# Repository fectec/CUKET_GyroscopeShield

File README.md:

# MO-2 Gyroscope Verification Shield

<p align="justify">
The PCB is designed as a shield for the NUCLEO-F446RET6, mechanically capable of stacking directly on top of the development board. This configuration routes all power and communication signals from the microcontroller to the peripheral components without the need for external jumper wires.
</p>

<p align="center">

  <br>

  <br>
  <em>Figure 1: PCB manufacturing and integration stages.</em>
</p>

<p align="center">

  <br>

  <br>
  <em>Figure 2: Lateral profiles of the soldered system.</em>
</p>

<p align="justify">
The communication architecture relies on two distinct protocols: I<sup>2</sup>C for the Pmod gyroscope interface and SPI for the flash memory. Table 1 details the point-to-point wiring between the Pmod J2 connector and the NUCLEO headers.
</p>

| Pmod Pin | Function | NUCLEO Pin |
| :--- | :--- | :--- |
| J2 Pin 5 | SCL | PB8 (I2C1_SCL) |
| J2 Pin 6 | SDA | PB9 (I2C1_SDA) |
| J2 Pin 7 | GND | GND |
| J2 Pin 8 | VCC | +3V3 |
<p align="justify"><em>Table 1: Pin mapping between Pmod Gyroscope (L3G4200D) and NUCLEO-F446RE.</em></p>

<p align="justify">
For the data logging subsystem, due to the complexity of the memory circuit, Table 2 lists only the utilized microcontroller pins. For complete electrical connections, refer to the schematic diagram in Figure 3.
</p>

| NUCLEO Pin (Function) |
| :--- |
| PB14 (SPI2_MISO) |
| PB15 (SPI2_MOSI) |
| PC7 (SPI2_SCLK) |
| PA4 (Chip Select) |
| GND |
| +3V3 (Flash Memory Power Supply) |
<p align="justify"><em>Table 2: NUCLEO-F446RE Pin assignment for SPI Flash Memory interface.</em></p>

<p align="justify">
The power subsystem is designed around an LM2596 step-down switching regulator. This component regulates the input voltage from a main battery pack—comprising two Lithium-Ion cells—to a stable 5V output required to power the NUCLEO board.
</p>

<p align="justify">
Additionally, the PCB integrates essential user interface components for operational control: a mechanical toggle switch for main power isolation, a status LED to provide visual feedback during algorithm execution, and a push-button connected via a long cable. The button serves as a manual logic input, facilitating control over the state of the system during the thermal chamber test setup.
</p>

<p align="center">
  
  <br>
  <em>Figure 3: Electrical Schematic of the MO-2 Gyroscope Verification Shield.</em>
</p>

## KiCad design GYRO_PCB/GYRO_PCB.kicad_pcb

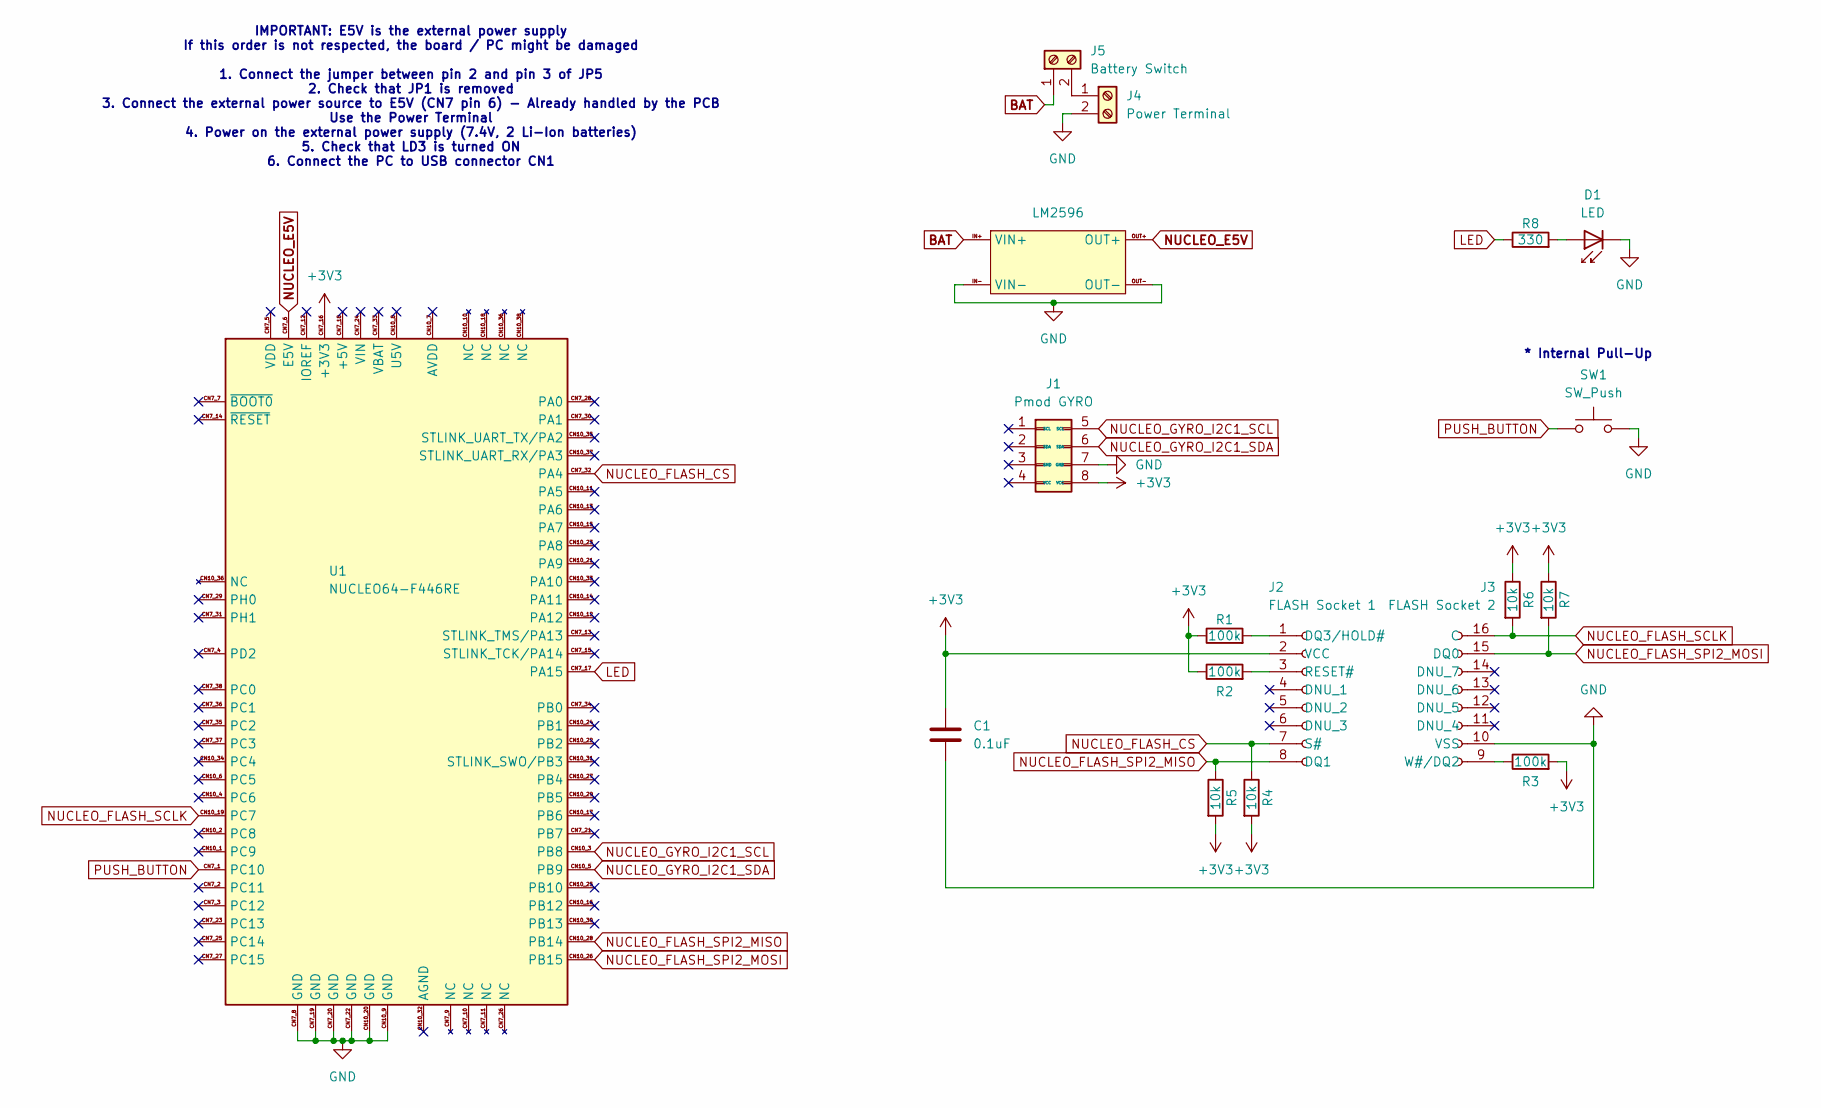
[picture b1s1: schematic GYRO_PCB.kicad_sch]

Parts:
C1: 0.1uF; C_Disc_D8.0mm_W2.5mm_P5.00mm
D1: LED; LED_D5.0mm_IRBlack
J1: Pmod GYRO; PinSocket_2x04_P2.54mm_Vertical_Custom
J2: FLASH Socket 1; PinSocket_1x08_P2.54mm_Vertical
J3: FLASH Socket 2; PinSocket_1x08_P2.54mm_Vertical_Custom
J4: Power Terminal; TerminalBlock_MaiXu_MX126-5.0-02P_1x02_P5.00mm
J5: Battery Switch; TerminalBlock_MaiXu_MX126-5.0-02P_1x02_P5.00mm
LM2596: LM2596 Module
R1, R2, R3: 100k; R_Axial_DIN0207_L6.3mm_D2.5mm_P10.16mm_Horizontal
R4, R5, R6, R7: 10k; R_Axial_DIN0207_L6.3mm_D2.5mm_P10.16mm_Horizontal
R8: 330; R_Axial_DIN0207_L6.3mm_D2.5mm_P10.16mm_Horizontal
SW1: SW_Push; PinSocket_1x02_P2.54mm_Vertical
U1: NUCLEO64-F446RE; NUCLEO-F446RE

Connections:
+3V3: C1.1, J1.8 (VCC), J2.2 (VCC), R1.1, R2.1, R3.2, R4.2, R5.2, R6.1, R7.1, U1.CN7_16 (+3V3)
BAT: J5.1, LM2596.IN+ (VIN+)
GND: C1.2, D1.1 (K), J1.7 (GND), J3.10 (VSS), J4.2, LM2596.IN- (VIN-), LM2596.OUT-, SW1.2, U1.CN7_8 (GND), U1.CN7_19 (GND), U1.CN7_20 (GND), U1.CN7_22 (GND), U1.CN10_9 (GND), U1.CN10_20 (GND)
LED: R8.1, U1.CN7_17 (PA15)
NUCLEO_E5V: LM2596.OUT+, U1.CN7_6 (E5V)
NUCLEO_FLASH_CS: J2.7 (S#), R4.1, U1.CN7_32 (PA4)
NUCLEO_FLASH_SCLK: J3.16 (C), R6.2, U1.CN10_19 (PC7)
NUCLEO_FLASH_SPI2_MISO: J2.8 (DQ1), R5.1, U1.CN10_28 (PB14)
NUCLEO_FLASH_SPI2_MOSI: J3.15 (DQ0), R7.2, U1.CN10_26 (PB15)
NUCLEO_GYRO_I2C1_SCL: J1.5 (SCL), U1.CN10_3 (PB8)
NUCLEO_GYRO_I2C1_SDA: J1.6 (SDA), U1.CN10_5 (PB9)
unnamed: D1.2 (A), R8.2
unnamed: J2.1 (DQ3/HOLD#), R1.2
unnamed: J2.3 (RESET#), R2.2
unnamed: J3.9 (W#/DQ2), R3.1
unnamed: J4.1, J5.2
PUSH_BUTTON: SW1.1, U1.CN7_1 (PC10)

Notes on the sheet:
IMPORTANT: E5V is the external power supply If this order is not respected, the board / PC might be damaged 1. Connect the jumper between pin 2 and pin 3 of JP5 2. Check that JP1 is removed 3. Connect the external power source to E5V (CN7 pin 6) - Already handled by the PCB Use the Power Terminal 4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
* Internal Pull-Up

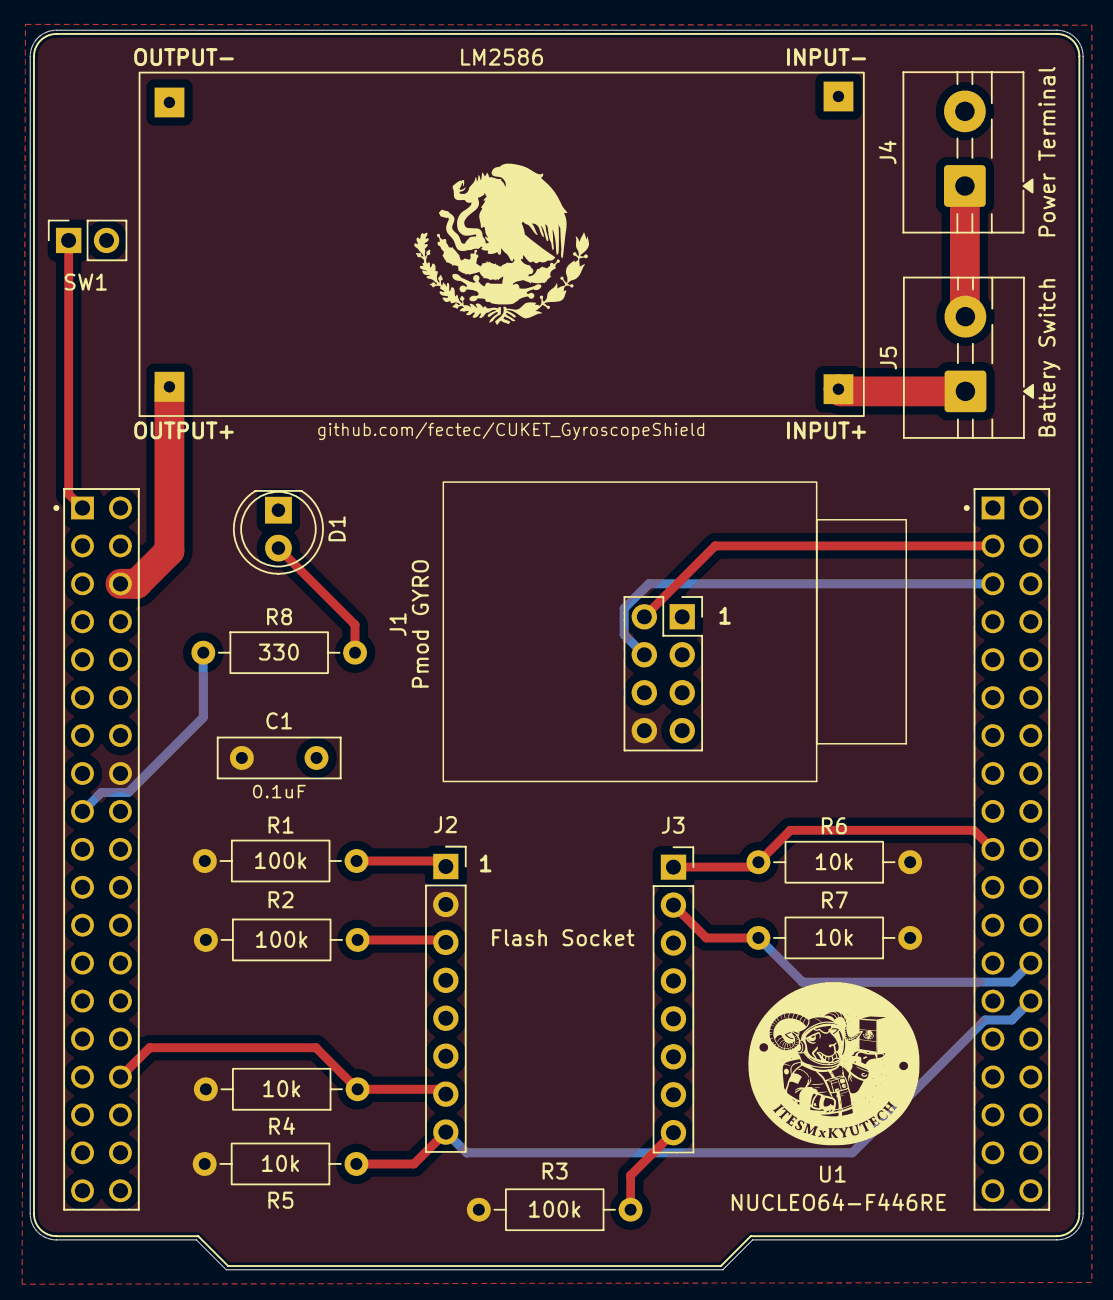
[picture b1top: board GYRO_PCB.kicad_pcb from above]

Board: 2 copper layers, 70.5 x 83.0 mm, 18 parts (0 on the bottom side), 17 nets.

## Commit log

2025-10-23 feat: add .gitignore file for temporary and export files
2025-10-23 feat: add footprint + symbol + 3D model for NUCCLEO-F446RE
2025-10-23 feat: add kicad project
2025-10-23 feat: add symbols and footprints for principal components
2025-10-23 feat: most of schematic done
2025-10-23 feat: finish PCB draft
2025-10-23 feat: add NUCLEO 3D model
2025-10-24 New schematic
2025-10-24 new pcb and schematic
2025-10-25 updated footprint for LED
2025-10-26 refactor: clean schematic & PCB + feat: add LM2596 & terminal 3D models
2025-10-27 fabrication files
2025-11-05 fix: correct DRC & add mechanical limits to gyroscope
2025-11-05 feat: add flash socket height
2025-11-12 feat: add push button
2025-11-12 feat: routing done
2025-11-12 feat: add footprints
2025-11-12 fix: change logo
2025-11-12 fix: last revision complete - ready to order
2025-12-02 feat: add README file
